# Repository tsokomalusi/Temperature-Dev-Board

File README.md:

# Project Requirements/Problem Statement
[Challenge](https://github.com/tsokomalusi/Temperature-Dev-Board/blob/main/%F0%9F%A7%A9%20Course%201%20%E2%80%94%20Temperature%20Monitor%20Dev%20Board%20-%20Course%201%20%E2%80%94%20Temperature%20Monitor%20STM32%20Dev%20Board%20%C2%B7%20The%20PCB%20Learning%20Collective.pdf)

# Temperature-Dev-Board

STM32-based temperature monitoring board featuring:

 10k NTC thermistor
- ADC temperature measurement
- OLED display
- USB power
- Expansion headers

## Hardware

- MCU: STM32
- Sensor: 10k NTC Thermistor
- Display: OLED
- 
## Schematic
The proposed schematic for this PCB Design challenge can be found within this repository
[Schematic](https://github.com/tsokomalusi/Temperature-Dev-Board/blob/main/Temperature_Monitoring_Dev_Board.pdf)

## Images

### BLOCK DIAGRAM

### 3D MODEL (TOP & BOTTOM VIEW)

### PCB LAYER (2 LAYER)

PCB STACKUP (2 LAYER)

L1: Signal/POWER
L2: GND

## Manufacturing

Gerber files are located in the manufacturing folder.

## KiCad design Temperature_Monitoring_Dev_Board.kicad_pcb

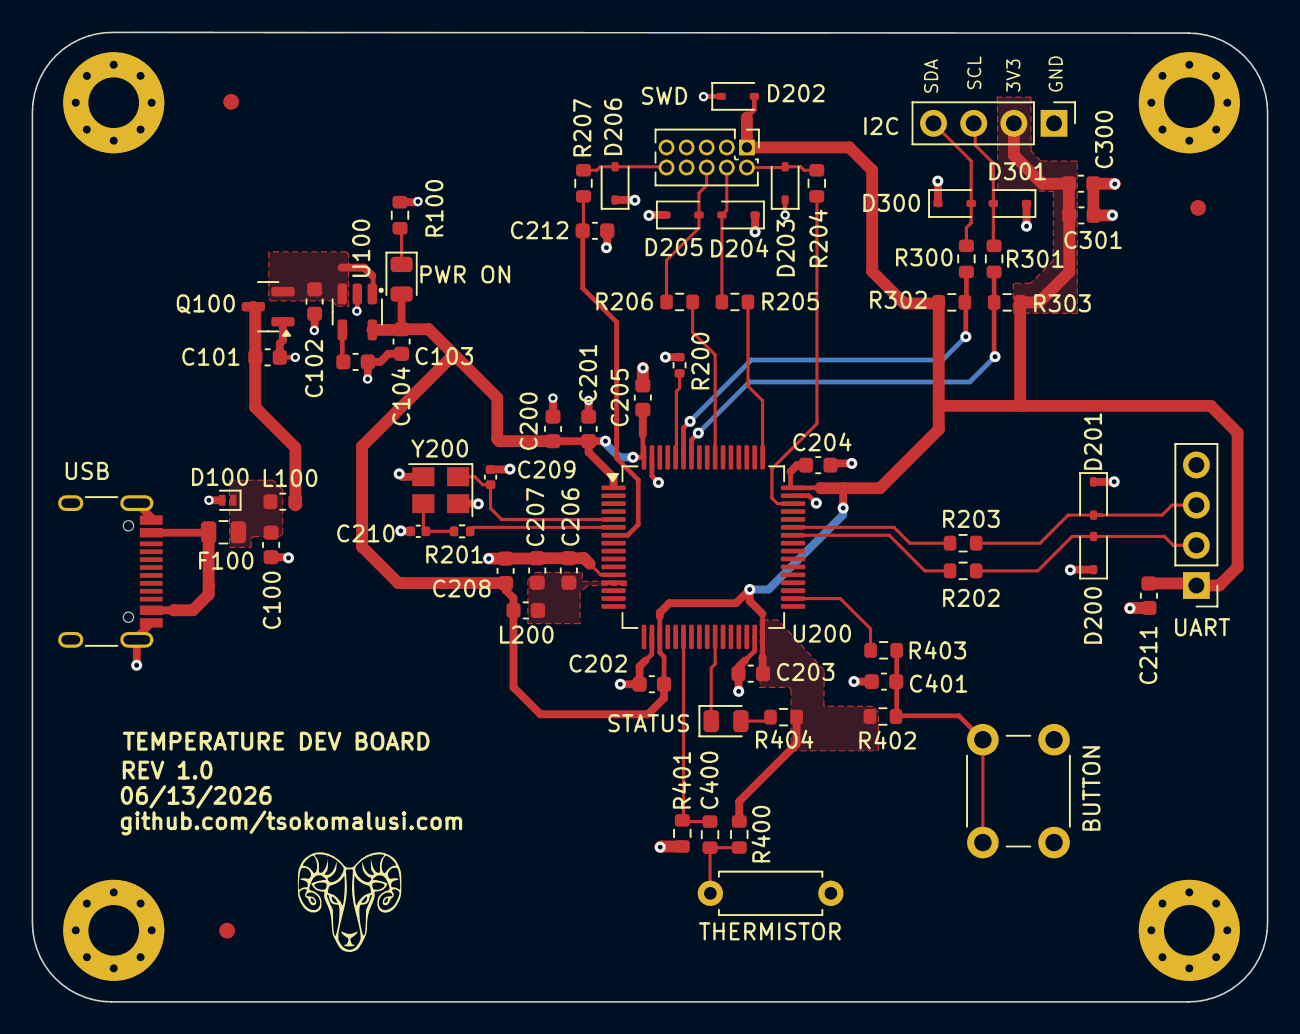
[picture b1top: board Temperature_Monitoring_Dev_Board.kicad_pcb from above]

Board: 2 copper layers, 78.1 x 61.3 mm, 73 parts (0 on the bottom side), 35 nets.

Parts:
BUTTON: SW_Push; SW_PUSH_6mm
C100, C101, C207, C208: 1u; C_0603_1608Metric
C102, C104, C200: 10u; C_0603_1608Metric
C103, C201, C202, C203, C204, C205, C211, C212, C300, C401: 100n; C_0603_1608Metric
C206: 10n; C_0603_1608Metric
C209, C210: 10p; C_0402_1005Metric
C301: 4u7; C_0603_1608Metric
C400: 100n; R_0603_1608Metric
D100: D_Zener; D_SOD-882
D200, D201, D202, D203, D204, D205, D206, D300, D301: PESD3V3L1BA,115; D_SOD-323
F100: 750mA; Fuse_0805_2012Metric
FID1, FID2, FID3: Fiducial; Fiducial_1mm_Mask2mm
H1, H2, H3, H4: MountingHole_Pad; MountingHole_3.2mm_M3_Pad_Via
I2C: OLED SSD1306; PinHeader_1x04_P2.54mm_Vertical
L100: 10n; L_0603_1608Metric
L200: 10n; C_0603_1608Metric
PWR ON: LED; D_0805_2012Metric
Q100: AO3401A; SOT-23
R100, R404: 1K; R_0603_1608Metric
R200: 10K; R_0402_1005Metric
R201: 0R; R_0402_1005Metric
R202, R203, R204, R205, R206, R207, R300, R301: 33R; R_0603_1608Metric
R302, R303: 4K7; R_0603_1608Metric
R400, R402: 10K; R_0603_1608Metric
R401, R403: 100R; R_0603_1608Metric
STATUS: BLUE; D_0805_2012Metric
SWD: 2X5X1.27 mm; PinHeader_2x05_P1.27mm_Vertical
THERMISTOR: Thermistor_NTC; R_Axial_DIN0207_L6.3mm_D2.5mm_P7.62mm_Horizontal
U100: SPX3819M5-L-3-3; SOT-23-5
U200: STM32F107RCT6; LQFP-64_10x10mm_P0.5mm
UART: Conn_01x04_Pin; PinHeader_1x04_P2.54mm_Vertical
USB: USB_C_Receptacle_USB2.0_16P; USB_C_Receptacle_HRO_TYPE-C-31-M-12
Xigote_Log: LOGO; Footprint_logos
Y200: 16MHz; Crystal_SMD_3225-4Pin_3.2x2.5mm

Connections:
+3V3: C104.1, C200.1, C201.1, C202.1, C203.1, C204.1, C205.1, C208.1, C211.1, C300.1, C301.1, D202.2 (A2), I2C.2, L200.2, PWR ON.2 (A), R302.1, R303.1, R400.1, R402.1, R404.1, SWD.1, U100.5 (OUT), U200.1 (VBAT), U200.19 (VDD), U200.32 (VDD), U200.48 (VDD), U200.64 (VDD), UART.1
+5V: C101.1, L100.2, Q100.3 (D)
+5VIN: C102.1, Q100.2 (S), U100.1 (IN), U100.3 (EN)
/Microcontroller/BOOT0: R200.2, U200.60 (BOOT0)
/Microcontroller/CONN_NRST: D206.2 (A2), R207.1, SWD.10
/Microcontroller/CONN_SWCLK: D204.2 (A2), R205.1, SWD.4
/Microcontroller/CONN_SWDIO: D203.2 (A2), R204.1, SWD.2
/Microcontroller/CONN_SWO: D205.2 (A2), R206.1, SWD.6
/Microcontroller/HSE_IN: C209.1, U200.5 (PD0), Y200.1
/Microcontroller/HSE_OUT: R201.2, U200.6 (PD1)
/Microcontroller/XTAL_IN: C210.1, R201.1, Y200.3
/Power Input/LED_PWR_K: PWR ON.1 (K), R100.1
ADC1_IN6: C400.1, R401.2, U200.22 (PA6)
BUTTON: R403.2, U200.34 (PB13)
GND: BUTTON.1, C100.2, C101.2, C102.2, C103.2, C104.2, C200.2, C201.2, C202.2, C203.2, C204.2, C205.2, C206.2, C207.2, C208.2, C209.2, C210.2, C211.2, C212.2, C300.2, C301.2, C400.2, C401.2, D100.2 (A), D200.1 (A1), D201.1 (A1), D202.1 (A1), D203.1 (A1), D204.1 (A1), D205.1 (A1), D206.1 (A1), D300.1 (A1), D301.1 (A1), H1.1, H2.1, H3.1, H4.1, I2C.1, Q100.1 (G), R100.2, R200.1, SWD.3, SWD.5, SWD.9, THERMISTOR.2, U100.2 (GND), U200.12 (VSSA), U200.18 (VSS), U200.31 (VSS), U200.47 (VSS), U200.63 (VSS), UART.4, USB.A1 (GND), USB.A12 (GND), USB.B1 (GND), USB.B12 (GND), USB.S1 (SHIELD), Y200.2, Y200.4
I2C1_SCL: R301.2, R303.2, U200.58 (PB6)
I2C1_SDA: R300.2, R302.2, U200.59 (PB7)
LED_STATUS: STATUS.1 (K), U200.26 (PB0)
NRST: C212.1, R207.2, U200.7 (NRST)
unnamed: BUTTON.2, C401.1, R402.2, R403.1
unnamed: D200.2 (A2), R202.1, UART.2
unnamed: D201.2 (A2), R203.1, UART.3
unnamed: D300.2 (A2), I2C.4, R300.1
unnamed: D301.2 (A2), I2C.3, R301.1
unnamed: R404.2, STATUS.2 (A)
unnamed: R400.2, R401.1, THERMISTOR.1
unnamed: C103.1, U100.4 (BP)
SWCLK: R205.2, U200.49 (PA14)
SWDIO: R204.2, U200.46 (PA13)
SWO: R206.2, U200.55 (PB3)
USART1_RX: R203.2, U200.43 (PA10)
USART1_TX: R202.2, U200.42 (PA9)
VBUS: C100.1, D100.1 (K), F100.2, L100.1
VBUS_CON: F100.1, USB.A4 (VBUS), USB.A9 (VBUS), USB.B4 (VBUS), USB.B9 (VBUS)
VDDA: C206.1, C207.1, L200.1, U200.13 (VDDA)

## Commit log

2026-06-14 Adding Images Folder
2026-06-14 added project requirements file
